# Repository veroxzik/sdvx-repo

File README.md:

# sdvx-repo

This repo contains all things Sound Voltex.
 
## Current Content

### Volume Assembly

These are full CAD models of the Valkyrie and Nemsys Volume Assemblies.

### Knobs

One replicating the AC knob, and one replicating the knob featured on a stock Virgoo Turbocharger.

### PCBs

A PCB designed to adapt generic hall effect pots to the same pinout as Sensatec pots.

## Donate

If you appreciate this repo or the other projects I do, you can make a monetary donation below. Thanks!

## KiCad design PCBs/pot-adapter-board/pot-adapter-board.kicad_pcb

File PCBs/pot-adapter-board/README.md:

## Pot Adapter Board

This board is designed to adapt generic hall effect potentiometers to use the same JST connector as Sensatec pots, such as the one used in the Sound Voltex volume knob assembly.

### Download

Download the gerbers from this folder, it is the only \*.zip file.

### Potentiometer

The potentiometer can be found by using various keywords such as "Non-contact Angle Sensor", "360 Degrees", "Digital Potentiometer".  
The manufacturer is listed on the pot as PandAuto and the part number is P3020-V1-CW360.  
One such link: https://www.aliexpress.com/item/4000112340019.html  

As of writing (2022-05) the price is about $20USD/ea.

### PCB

The PCB is designed to be a single layer. Standard board thickness (1.6mm) and all default options should suffice.

### JST Connector

The other component on the board is JST P/N S3B-ZR. This matches the connector on the Sensatec encoder, providing drop-in capabilities.

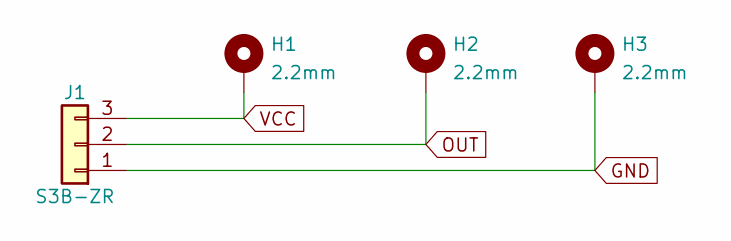
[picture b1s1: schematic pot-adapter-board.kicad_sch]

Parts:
H1, H2, H3: 2.2mm; MountingHole_2.2mm_M2_Pad_TopBottom
J1: S3B-ZR; JST_ZH_S3B-ZR_1x03_P1.50mm_Horizontal

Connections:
GND: H3.1, J1.1
OUT: H2.1, J1.2
VCC: H1.1, J1.3

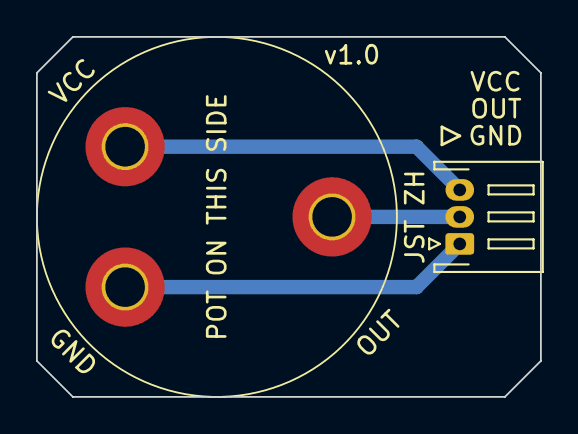
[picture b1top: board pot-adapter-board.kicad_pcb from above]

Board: 2 copper layers, 28.0 x 20.0 mm, 4 parts (0 on the bottom side), 3 nets.

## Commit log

2021-04-30 Added AC and Turbocharger knob models.
2021-04-30 Added images of knobs.
2021-04-30 Fix knob readme.
2021-04-30 Fix images (for real).
2022-05-08 Fix typo.
2022-05-08 Add pot adapter board.
2022-05-08 Added download clarification.
2022-05-08 Update main README.
2022-07-16 Add vol assy CAD, update AC knob model, README updates.
2023-01-17 Update Speedylabs URL, Add Blue Spring Express.
2023-05-04 SpeedyPotato | Valkyrie Knob Assembly
